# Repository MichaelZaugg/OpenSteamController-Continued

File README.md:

# Open Steam Controller - Continued

Welcome to the Open Steam Controller Continued Project!

This project is a fork of the [original Open Steam Controller](https://github.com/greggersaurus/OpenSteamController) by [Greg Gluszek](https://github.com/greggersaurus).

I hope to continue and improve upon the already amazing work done to deconstruct, document,
repurpose, and expand upon the Steam Controller firmware and hardware. As well as
provide a page of mods for those wanting to improve their own controllers with all
the information they need.

# The Steam Controller

The Steam Controller is a video game controller released by Valve Corporation
on November 10, 2015. This was part of Valve's initiative to give PC gamers the
option of a console-like experience.

Keeping some aspects familiar to modern video game controllers (i.e. a left analog stick,
four face buttons, two shoulder, and bumper buttons) while also changing up some of the
norms that we have come to expect (i.e. replacing the directional pad
and right analog stick with trackpads).

Additional details on the controller can be found on the official
[Product Page](https://store.steampowered.com/app/353370/Steam_Controller/)

# [Project Summary](./ProjectSummary.md)

Read about how this project came to be and the mind behind it.

# [Mods](./Mods/)

Take a look at some of the current mods for the Steam Controller in this directory.

# Notice and Warning

Please recognize that by utilizing any part of this project you are doing so at
your own risk. This is a reverse engineering effort and [we] make no claims to
have a complete understanding of the hardware [that we write] custom or modified
firmware for. Hopefully the testing [we] perform before publishing our findings and
modifications will prevent damage to your Steam Controller or anything you may
connect your Steam Controller to (i.e. the Nintendo Switch). However, [we] cannot
guarantee that.

Also please note this is being shared primarily for educational purposes. While
this may allow a user to do things such as use the Steam Controller on the
Nintendo Switch, please recognize that this is almost definitely going to be
coming with trade-offs compared to officially supported hardware and firmware.

Finally note that [we] say all of this with the hope of not discouraging anyone.
Please dive in and get your hands dirty. Just please be aware that there is a
(hopefully) very small, but non-zero, chance that a mistake could lead to
[bricked or broken hardware](./LoadingFirmware.md).

# Subproject Example

This section gives brief outlines and demonstrations (if applicable) of the
major efforts of this project. Further details on each Subproject can
be found in their respective directories.

## [Firmware](./Firmware/)

The work in this directory is geared towards creating a completely custom firmware
build for the Steam Controller. This project can be configured to have the
controller act as a development system that allows for querying peripherals
and exploring or verifying system behaviors. Additionally the project can
be configured for more practical purpose, such as behaving like a wired
Nintendo Switch controller.

Below are some videos demonstrating the different firmware builds:

Open Steam Controller: Nintendo Switch

Open Steam Controller: Development Board

# Contributing

This is an open source project, so please make use of this however you would
like (as long as it does not violate any licenses stated within).

If you would like to offer contributions back to this repo that would be great.
That could come in the form of issues/discussions on how this could be more
user friendly or by adding features or support that is not yet there.

Note that there are TODO documents for each Subproject. The idea
is to outline goals I would like to accomplish. If you want to help with any of
these that would be awesome. It would be even more awesome if you started a
conversation regarding your intentions so as to limit the chances of duplicated
effort or incongruous designs.

# Bugs and Issues

We will do our best to provide easy to use and robust software. However, there
will still most likely be bugs. If you find a bug, please report it.

The best way to report a bug is to use the Issues tab on GitHub.

When reporting a bug/issue, please make sure to provide sufficient details. Key
details to include are:

* Exactly what steps did you take?
* Can you reproduce the error by following your own steps?
* Do you have any files that make the bug occur (i.e. specific .musicxml file)?

# Resources and Influences

This section lists some projects that influenced this project, as well as links
to some resources that may continue to be helpful to stay current on.

## [Pilatomic Steam Controller Singer](https://gitlab.com/Pilatomic/SteamControllerSinger)

* Example of using the haptics to play music.
* Example of PC side code written in C using libusb.
* Allows for playing songs of any length, but at cost of controller being occupied by Singer software.

## [HID Joy-Con Whispering](https://github.com/shinyquagsire23/HID-Joy-Con-Whispering)

* Application for communicating with Pro Controller via USB HID.
* Helpful for Switch Faux Controller development to get USB communications in place.

## [Nintendo Switch Reverse Engineering](https://github.com/dekuNukem/Nintendo_Switch_Reverse_Engineering)

* Notes on Reverse Engineering of Nintendo Switch Controllers.
* Helpful details on HID communications with Pro Controller.

## [Standalone Steam Controller Driver](https://github.com/ynsta/steamcontroller)

* Source for breaking down some USB commands.
* Goal of this project is to be able to use Steam Controller as a game controller outside of the Steam platform.

## [Steam Controller Update News](http://store.steampowered.com/news/?appids=353370)

* Useful to get an idea of what changed from official firmware to firmware release.

## [UnBricking Steam Controller (Manual Firmware Update, Rollback)](https://steamcommunity.com/sharedfiles/filedetails/?id=572740074)

* Step by step guide on how to manually change the Steam Controller firmware.
* Much of this information is captured in [Loading Firmware](./LoadingFirmware.md).
  * [Loading Firmware](./LoadingFirmware.md) presents the information in the context of how it applies to Open Steam Controller Project and its Subprojects.

## Steam Communities

* [Official Group](http://steamcommunity.com/games/353370#announcements/detail/901091250587237164)
* [Custom Sounds Discussion](https://steamcommunity.com/app/353370/discussions/0/458607699626517823/)

# TODO

While a lot has been accomplished in this project thus far, there is still so much that
can be done with the Steam Controller (especially given the groundwork that has
been laid up to this point). In order to capture and track these ideas TODO documents
have been made for each Subproject. A good place to start is the top-level
[TODO Document](./TODO.md). This covers the highest level goals for the project
while providing links to Subproject specific TODOS.

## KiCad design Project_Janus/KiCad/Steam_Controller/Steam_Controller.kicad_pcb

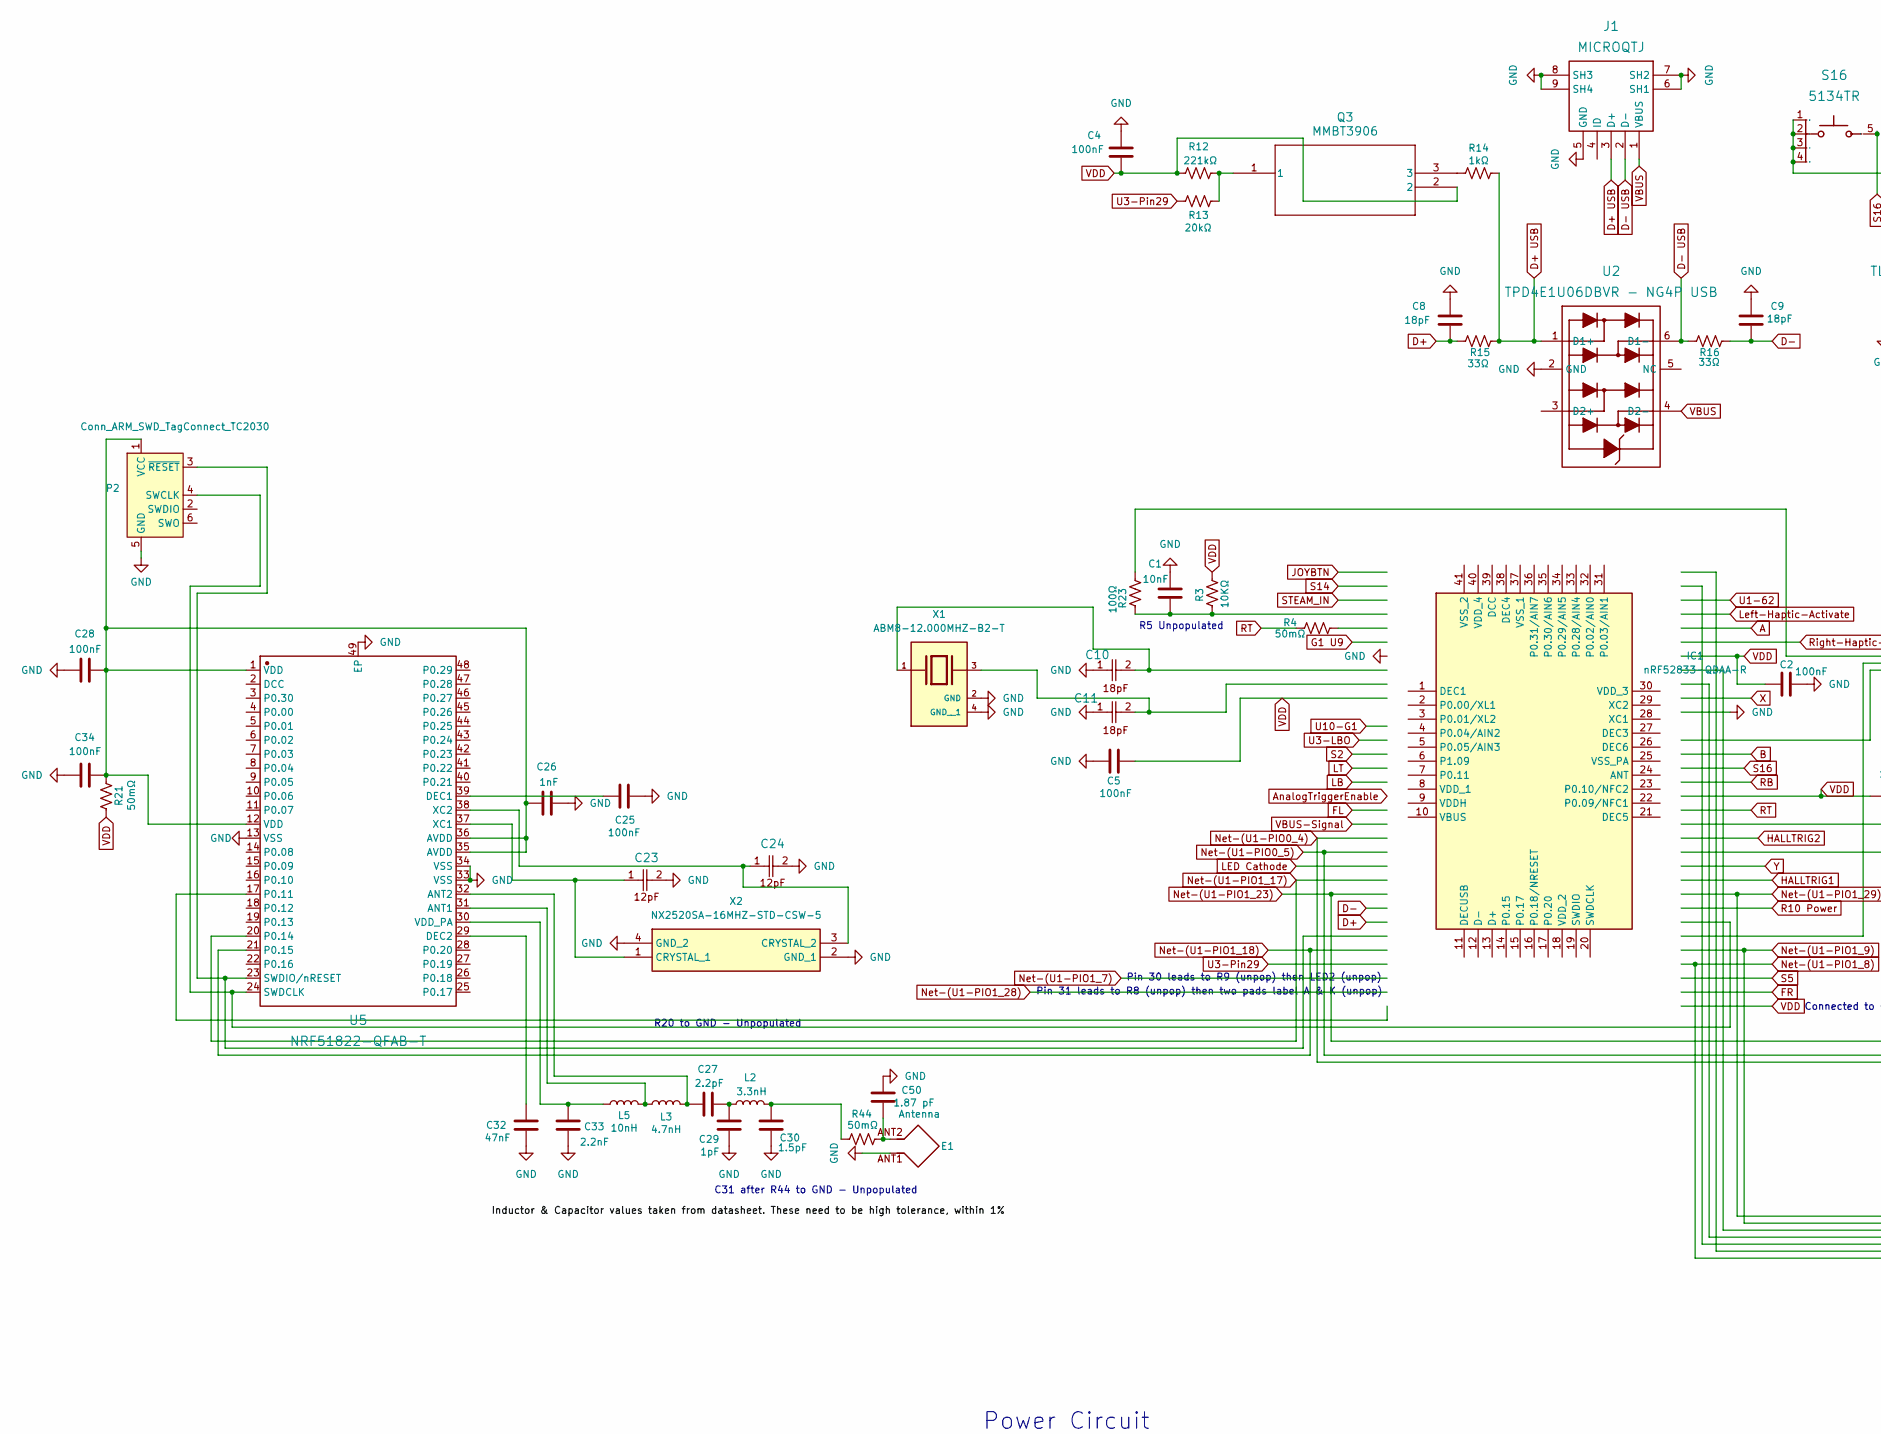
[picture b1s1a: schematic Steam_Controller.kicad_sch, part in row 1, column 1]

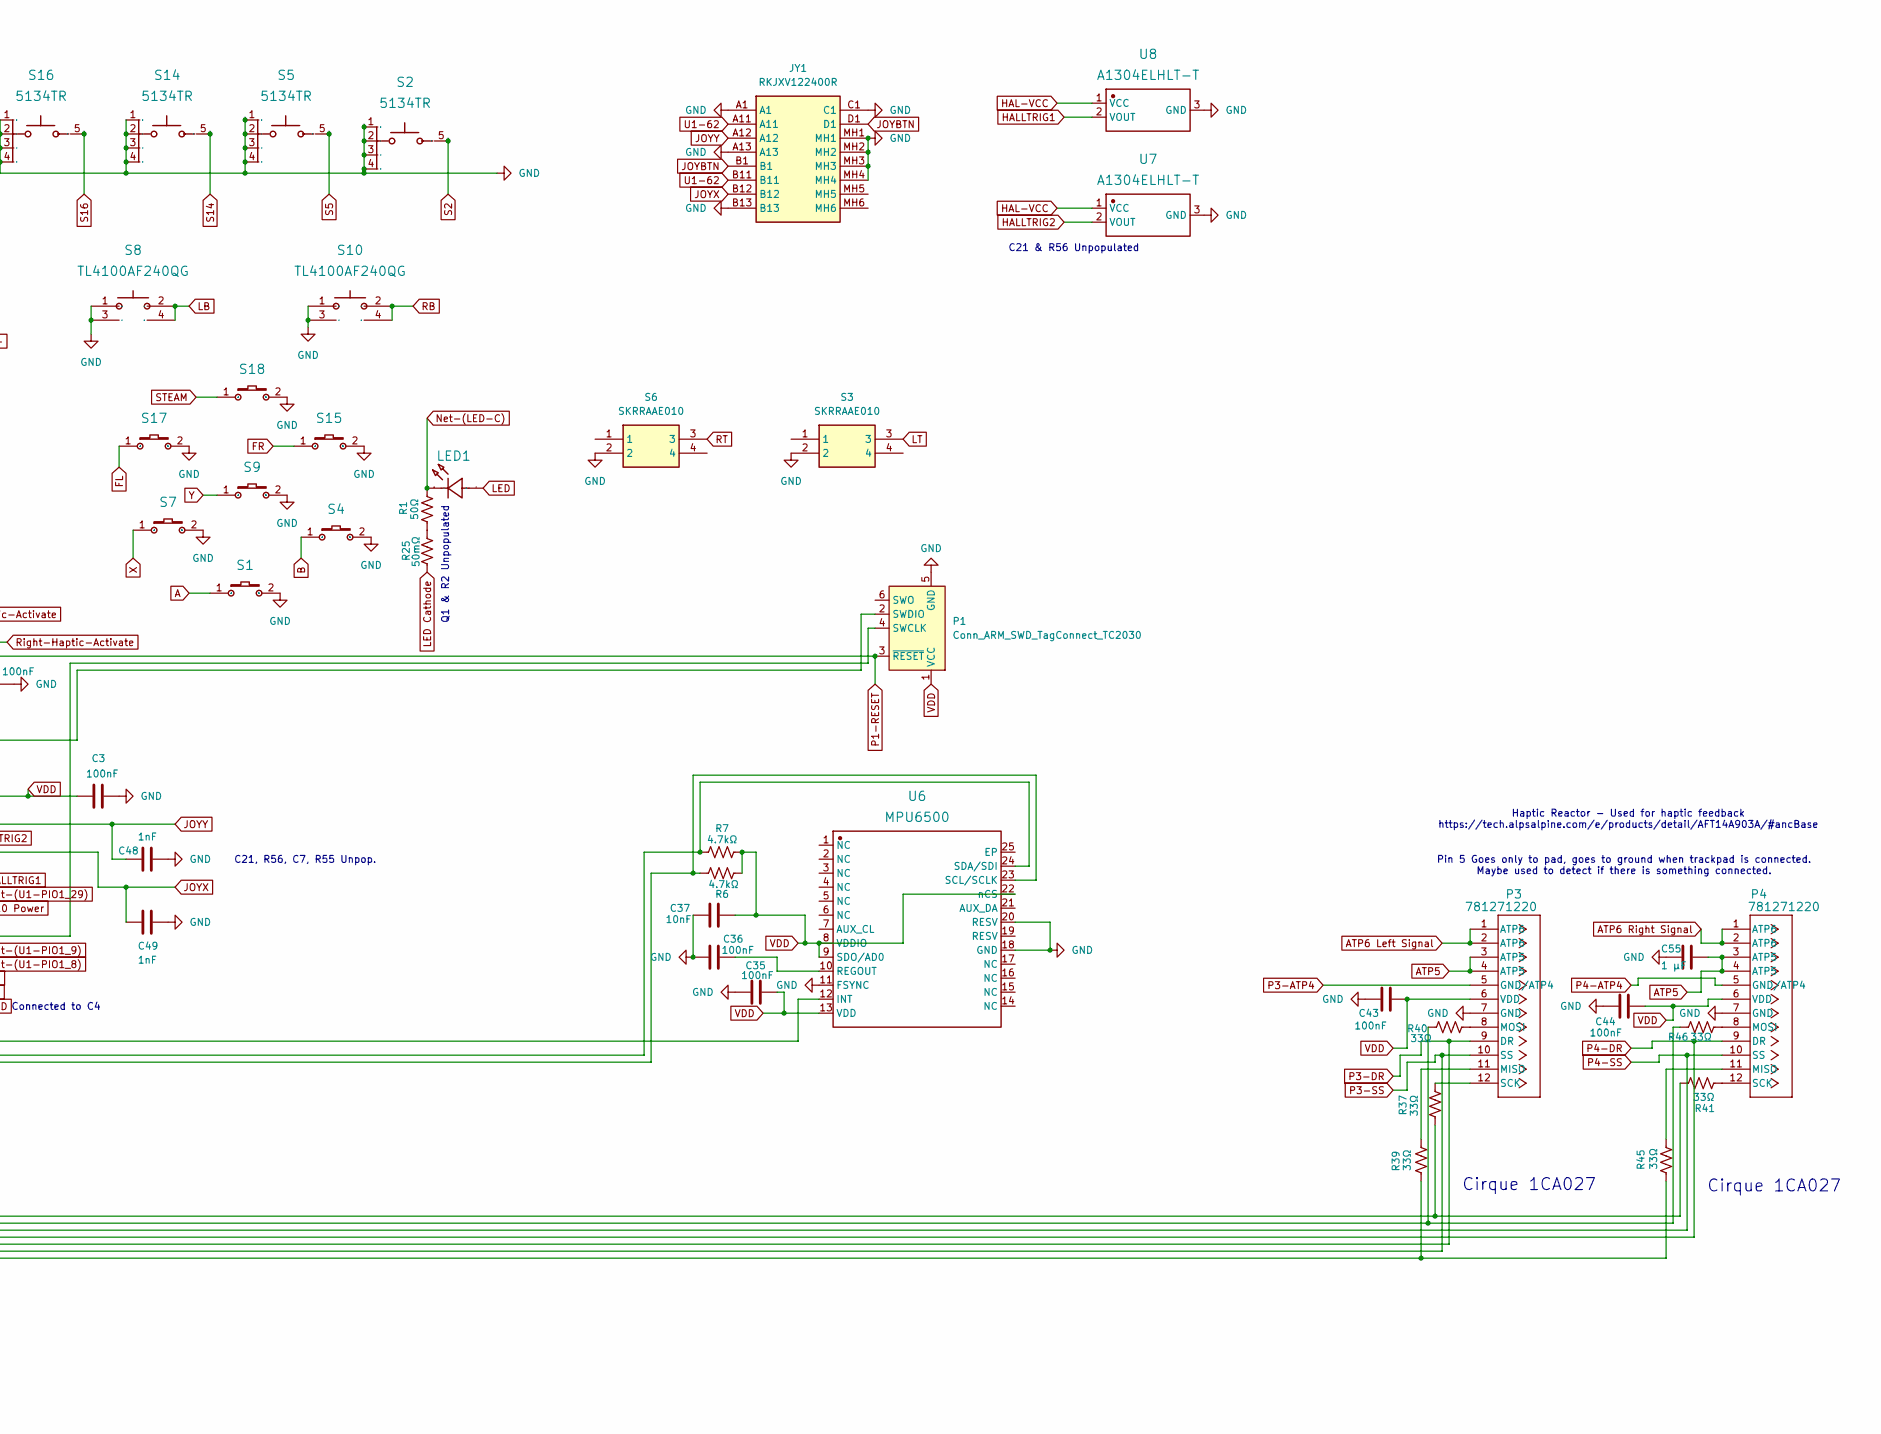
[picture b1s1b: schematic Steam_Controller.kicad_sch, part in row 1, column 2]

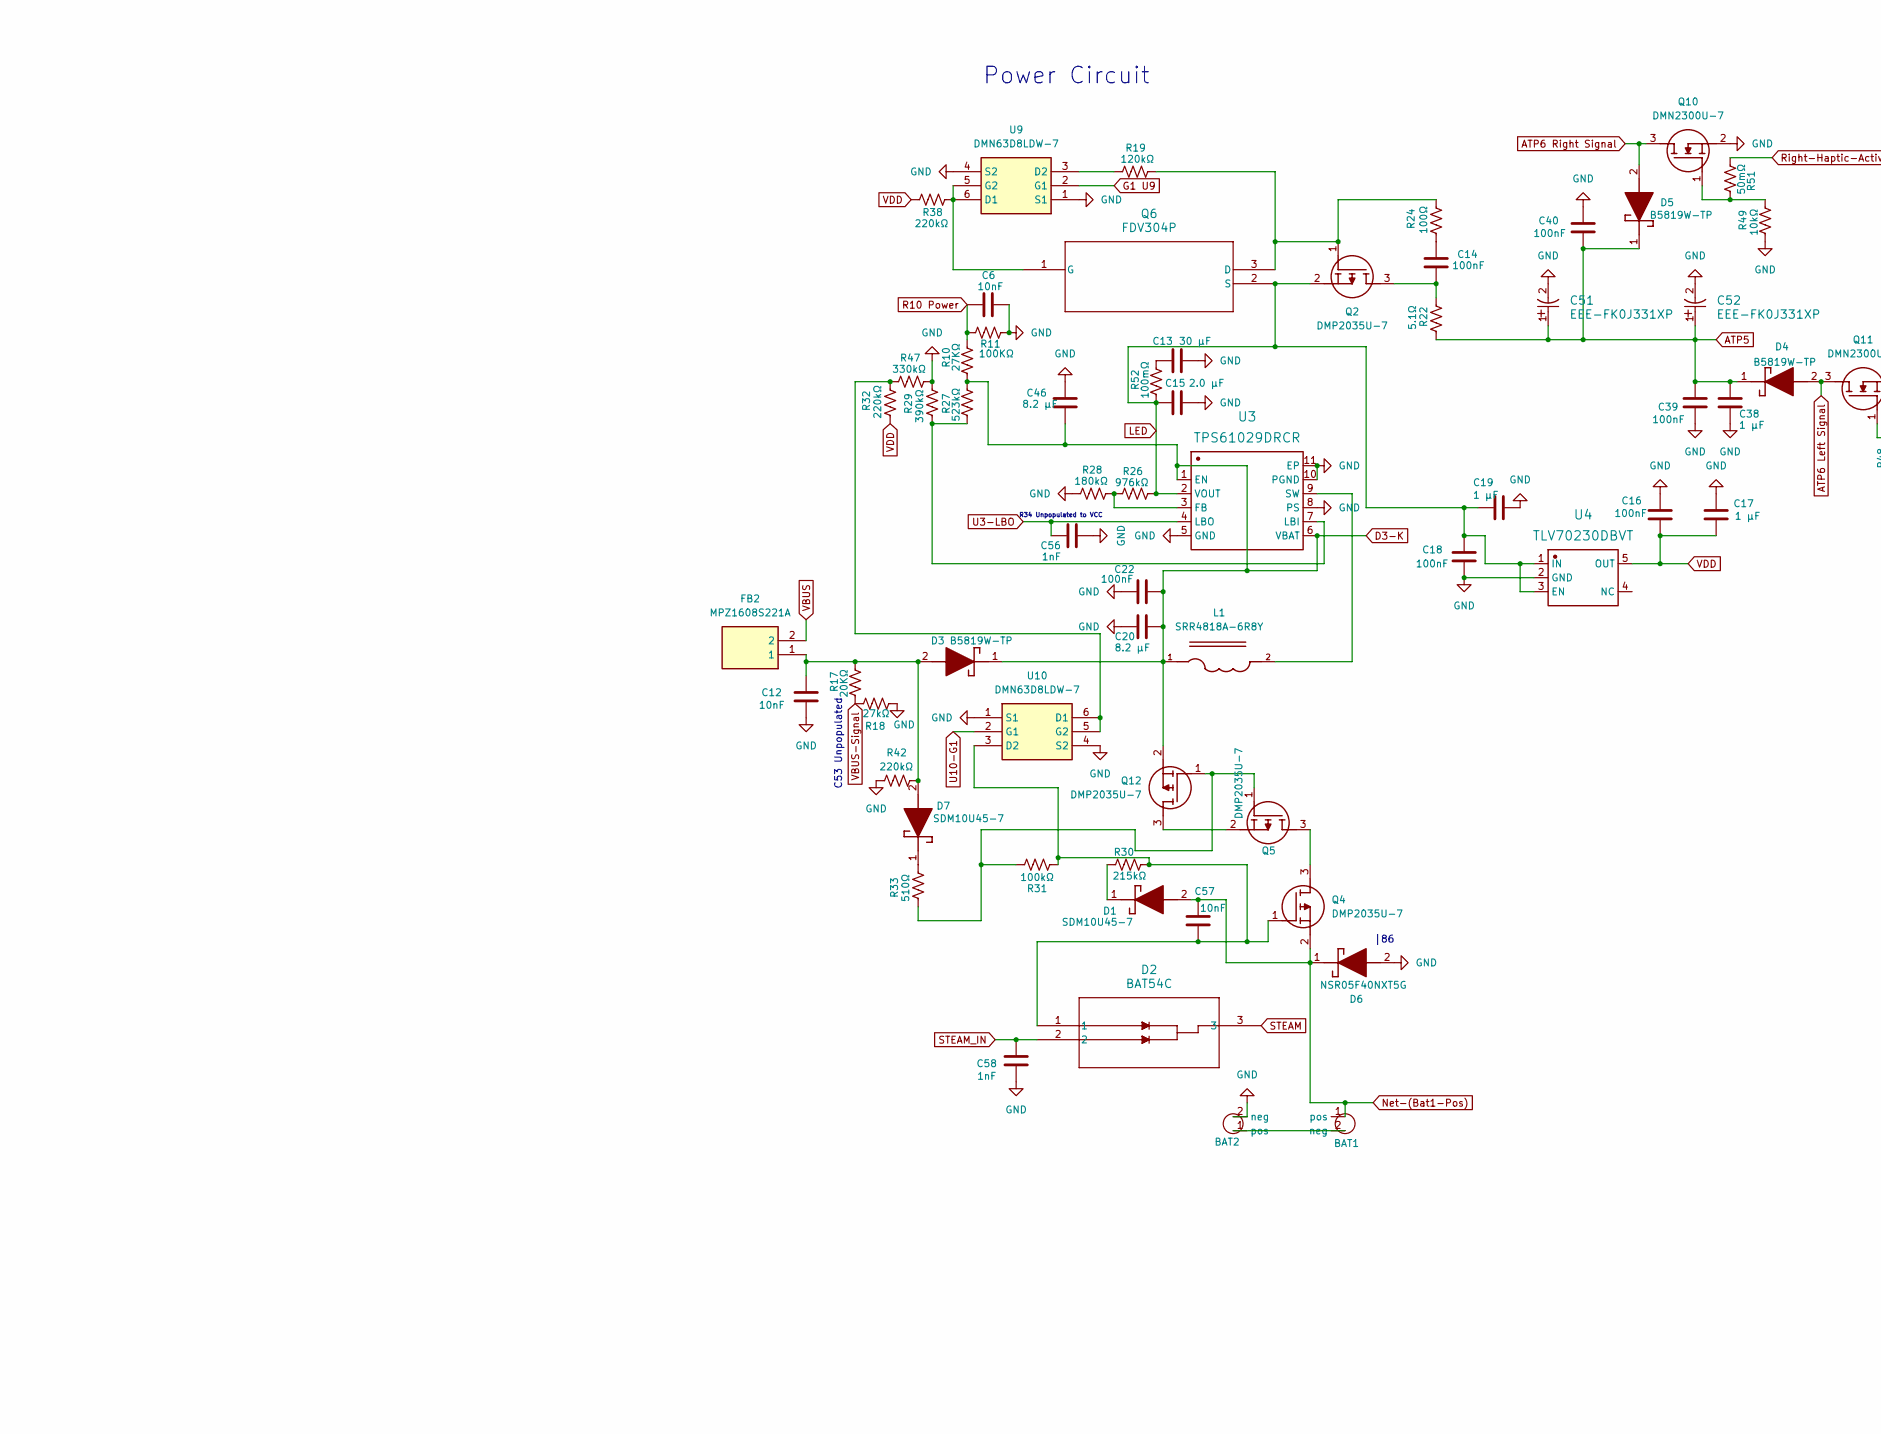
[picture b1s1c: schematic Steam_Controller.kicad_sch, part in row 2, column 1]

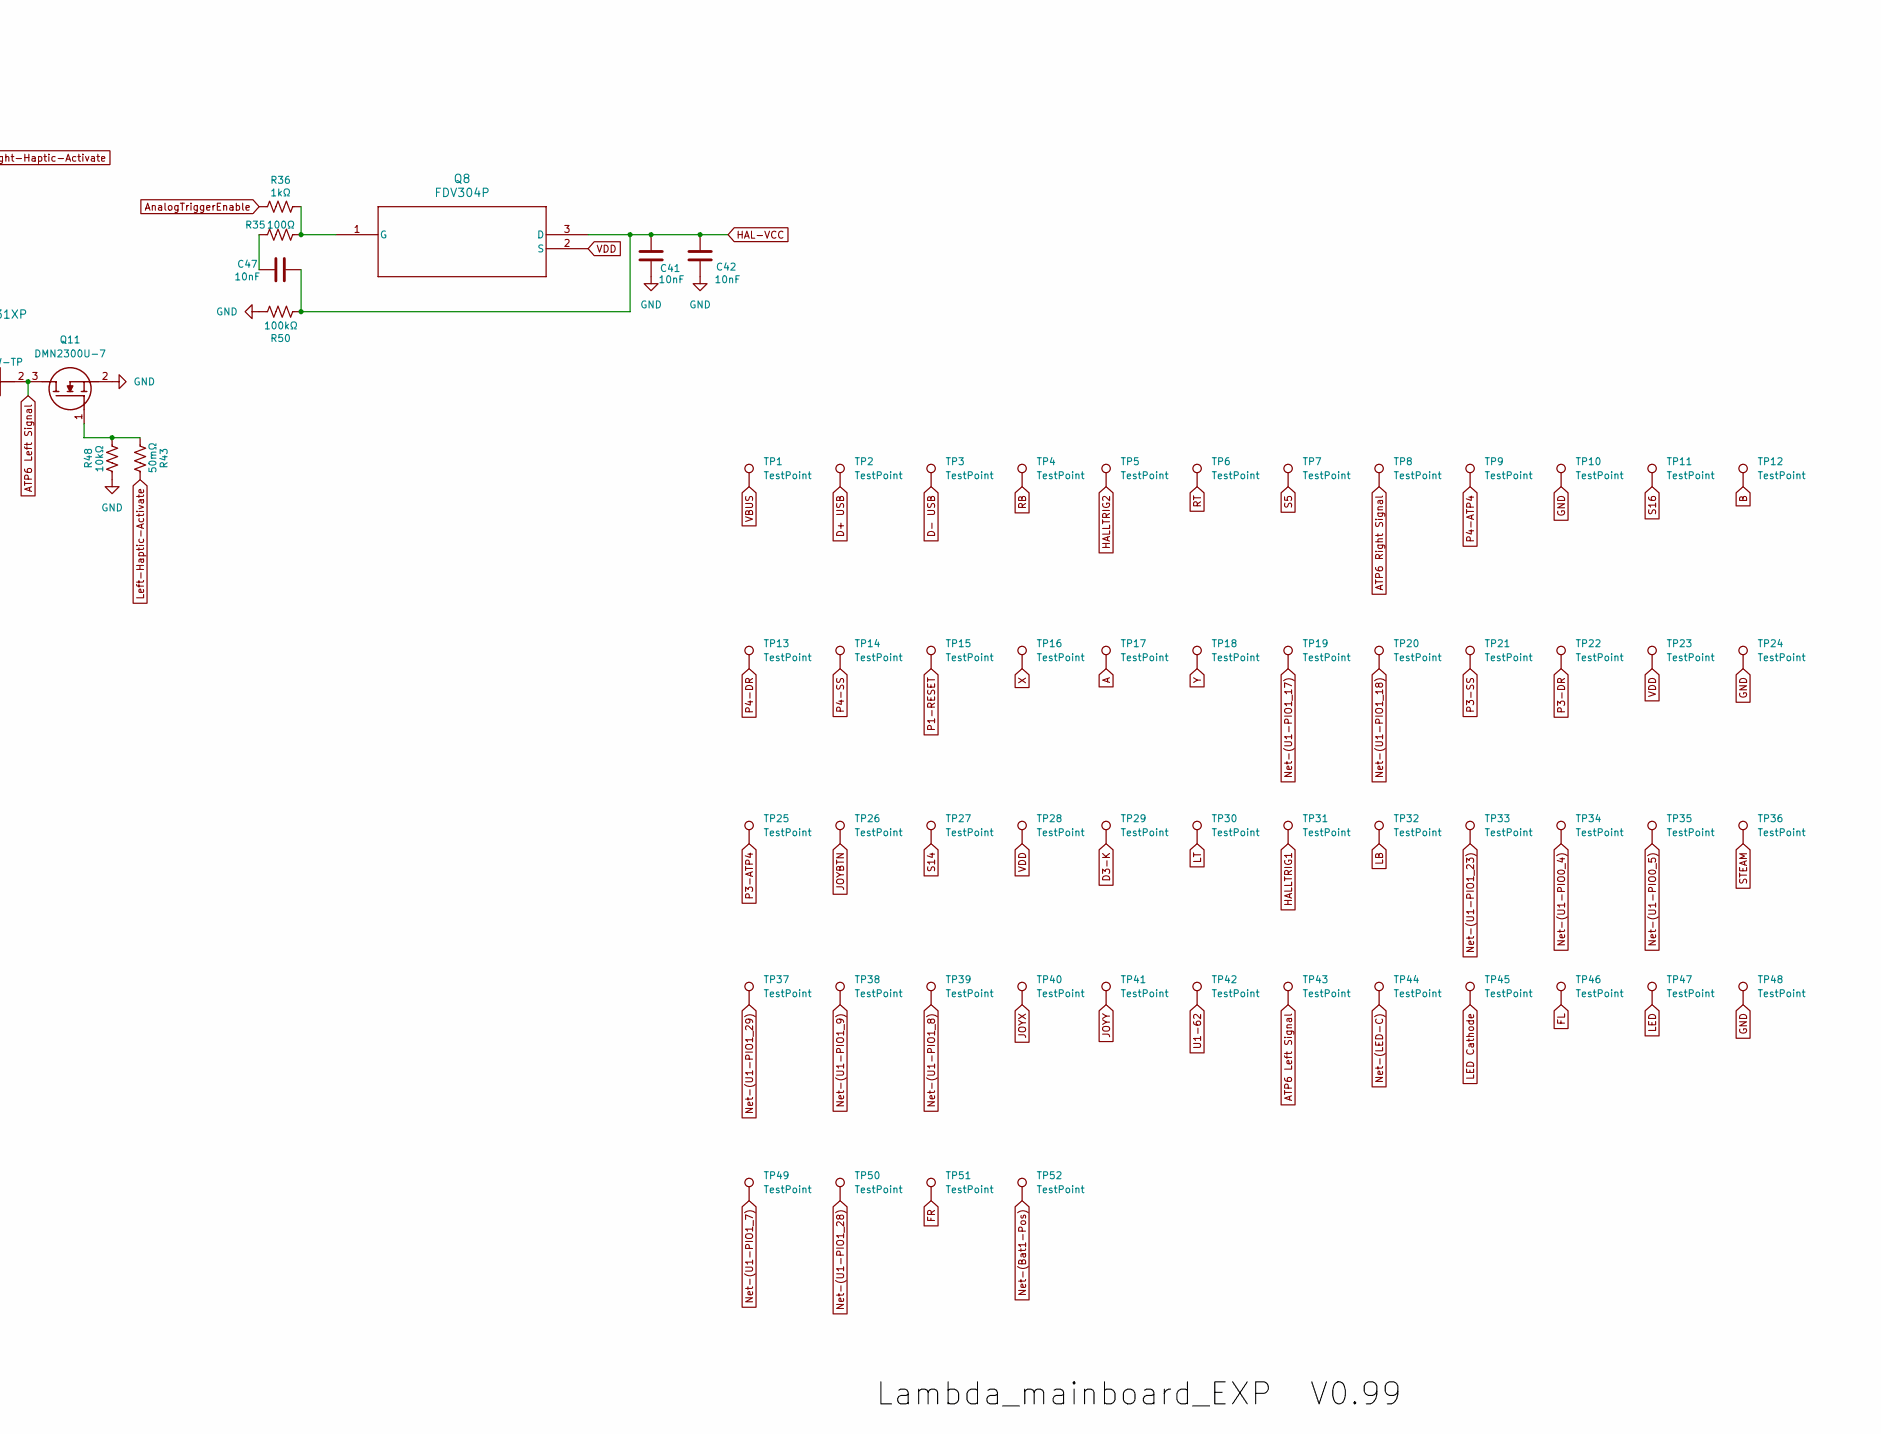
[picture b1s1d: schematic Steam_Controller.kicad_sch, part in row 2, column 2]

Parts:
BAT1, BAT2: BatteryPads
C1, C6, C12, C37, C41, C42, C47, C57: 10nF; C_0201_0603Metric
C2, C3, C4, C5, C14, C16, C18, C22, C25, C28, C34, C35, C36, C39, C43: 100nF; C_0201_0603Metric
C8, C9: 18pF; C_0201_0603Metric
C10, C11: C0402C180J3GACAUTO; C_0201_0603Metric
C13: 30 µF; C_1206_3216Metric
C15: 2.0 µF; C_0402_1005Metric
C17, C19, C38, C55: 1 µF; C_0402_1005Metric
C20, C46: 8.2 µF; C_0805_2012Metric
C23, C24: C0402C120F5GACTU; C_0201_0603Metric
C26, C48, C49, C56, C58: 1nF; C_0201_0603Metric
C27: 2.2pF; C_0201_0603Metric
C29: 1pF; C_0201_0603Metric
C30: 1.5pF; C_0201_0603Metric
C32: 47nF; C_0201_0603Metric
C33: 2.2nF; C_0201_0603Metric
C40, C44: 100nF; R_0201_0603Metric
C50: 1.87 pF; C_0201_0603Metric
C51, C52: EEE-FK0J331XP; CAP_EEFK_D8_PAN
D1, D7: SDM10U45-7; D_SOD-523; Mouser Part Number 621-SDM10U45
D2: BAT54C; SOT-23-3
D3, D4, D5: B5819W-TP; D_SOD-123; Mouser Part Number 833-B5819W-TP
D6: NSR05F40NXT5G; D_0201_0603Metric; Mouser Part Number 863-NSR05F40NXT5G
E1: Antenna; Antenna_footprint
FB2: MPZ1608S221A; L_0402_1005Metric; Mouser Part Number 810-MPZ1608S221A
IC1: nRF52833-QDAA-R; QFN40P500X500X90-41N; Manufacturer_Part_Number nRF52833-QDAA-R; Mouser Part Number 949-NRF52833-QDAA-R
J1: MICROQTJ; MICRO-USB-SMD_MICROQTJ-5P; Manufacturer Part MicroQTJ
JY1: RKJXV122400R; Mouser Part Number 688-RKJXV122400R
L1: SRR4818A-6R8Y; IND_SRR4818A-6R8Y; DigiKey_Part_Number SRR4818A-6R8YTR-ND
L2: 3.3nH; L_0201_0603Metric
L3: 4.7nH; L_0201_0603Metric
L5: 10nH; L_0201_0603Metric
LED1: E6C0805WWAY1UDA(1.1T_M); LED0805-RD_WHITE; Manufacturer Part E6C0805WWAY1UDA(1.1T M)
P1, P2: Conn_ARM_SWD_TagConnect_TC2030; Tag-Connect_TC2030-IDC-FP_2x03_P1.27mm_Vertical
P3, P4: 781271220; CON_781271220
Q2, Q4, Q5, Q12: DMP2035U-7; SOT-23-3; Manufacturer_Part_Number DMP2035U-7
Q3: MMBT3906; SOT-23-3
Q6, Q8: FDV304P; SOT-23-3
Q10, Q11: DMN2300U-7; SOT-23-3; Mouser Part Number 621-DMN2300U-7
R1: 50Ω; R_0201_0603Metric
R3: 10KΩ; R_0201_0603Metric
R4, R21, R25, R43, R44, R51: 50mΩ; R_0201_0603Metric
R6, R7: 4.7kΩ; R_0201_0603Metric
R10: 27KΩ; R_0201_0603Metric
R11: 100KΩ; R_0201_0603Metric
R12: 221kΩ; R_0201_0603Metric
R13: 20kΩ; R_0201_0603Metric
R14, R36: 1kΩ; R_0201_0603Metric
R15, R16, R37, R39, R40, R41, R45, R46: 33Ω; R_0201_0603Metric
R17: 20KΩ; R_0201_0603Metric
R18: 27kΩ; R_0201_0603Metric
R19: 120kΩ; R_0201_0603Metric
R22: 5.1Ω; R_1206_3216Metric
R23, R24, R35: 100Ω; R_0201_0603Metric
R26: 976kΩ; R_0201_0603Metric
R27: 523kΩ; R_0201_0603Metric
R28: 180kΩ; R_0201_0603Metric
R29: 390kΩ; R_0201_0603Metric
R30: 215kΩ; R_0201_0603Metric
R31, R50: 100kΩ; R_0201_0603Metric
R32, R38, R42: 220kΩ; R_0201_0603Metric
R33: 510Ω; R_0201_0603Metric
R47: 330kΩ; R_0201_0603Metric
R48, R49: 10kΩ; R_0201_0603Metric
R52: 100mΩ; R_0603_1608Metric
S1, S4, S7, S9, S15, S17: Steam_Controller_ButtonPads; BUTTONPADS
S2, S5, S14, S16: 5134TR; SW_5134TR
S3, S6: SKRRAAE010; SKRR; Mouser Part Number 688-SKRRAA
S8, S10: TL4100AF240QG; SW-SMD_TL4100AF240QG; Manufacturer Part TL4100AF240QG
S18: STEAM_Symbol; STEAM
TP1, TP2, TP3, TP4, TP5, TP6, TP7, TP8, TP9, TP10, TP11, TP12, TP13, TP14, TP15, TP16, TP17, TP18, TP19, TP20, TP21, TP22, TP23, TP24, TP25, TP26, TP27, TP28, TP29, TP30, TP31, TP32, TP33, TP34, TP35, TP36, TP37, TP38, TP39, TP40, TP41, TP42, TP43, TP44, TP45, TP46, TP47, TP48, TP49, TP50, TP51, TP52: TestPoint; Steam Controller Test Pad
U2: TPD4E1U06DBVR - NG4P USB; SOT-23-6; Manufacturer Part TPD4E1U06DBVR
U3: TPS61029DRCR; VSON-10-1EP_3x3mm_P0.5mm_EP1.2x2mm; Manufacturer Part TPS61029DRCR
U4: TLV70230DBVT; SOT-23-5; Manufacturer Part TLV70230DBVT
U5: NRF51822-QFAB-T; QFN-48_L6.0-W6.0-P0.40-TL-EP4.6; Manufacturer Part NRF51822-QFAB-T
U6: MPU6500; QFN-24_L3.0-W3.0-P0.40-BL-EP; Manufacturer Part MPU-6500
U7, U8: A1304ELHLT-T; SOT-23W; Manufacturer Part A1304ELHLT-T
U9, U10: DMN63D8LDW-7; SOT-363_SC-70-6; Mouser Part Number 621-DMN63D8LDW-7
X1: ABM8-12.000MHZ-B2-T; XTAL_ABM8-12.000MHZ-B2-T; PARTREV 44041
X2: NX2520SA-16MHZ-STD-CSW-5; NX2520SA16MHZSTDCSW5; Mouser Part Number 344-NX2520SA16MCSW5

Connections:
A: S1.1 (1_in), TP17.1 (1_1)
ATP5: C38.1, C39.1, C40.1, C51.1, C52.1, C55.1, D4.1 (K), D5.1 (K), P3.3 (ATP5), P3.4 (ATP5), P4.3 (ATP5), P4.4 (ATP5), R22.2
ATP6 Left Signal: D4.2 (A), P3.1 (ATP6), P3.2 (ATP6), Q11.3 (D), TP43.1 (1_1)
ATP6 Right Signal: D5.2 (A), P4.1 (ATP6), P4.2 (ATP6), Q10.3 (D), TP8.1 (1_1)
AnalogTriggerEnable: R36.2
B: S4.1 (1_in), TP12.1 (1_1)
D3-K: C20.1, C22.2, C46.2, D3.1 (K), L1.1, Q12.2 (S), R10.2, R27.1, TP29.1 (1_1), U3.1 (EN), U3.6 (VBAT)
D+: C8.1, R15.2
D+ USB: J1.3 (D+), R14.1, R15.1, TP2.1 (1_1), U2.1 (D1+)
D-: C9.1, R16.1
D- USB: J1.2 (D-), R16.2, TP3.1 (1_1), U2.6 (D1-)
FL: S17.1 (1_in), TP46.1 (1_1)
FR: S15.1 (1_in), TP51.1 (1_1)
G1 U9: U9.2 (G1)
GND: BAT2.2 (neg), C1.1, C2.1, C3.1, C4.2, C5.1, C6.1, C8.2, C9.2, C10.1, C11.1, C12.1, C13.1, C15.1, C16.1, C17.1, C18.1, C19.1, C20.2, C22.1, C23.2, C24.2, C25.1, C26.1, C28.2, C29.2, C30.1, C32.2, C33.2, C34.2, C35.2, C36.2, C37.2, C38.2, C39.2, C40.2, C41.2, C42.2, C43.2, C44.2, C46.1, C48.1, C49.1, C50.2, C51.2, C52.2, C55.2, C56.1, C58.2, D6.2 (A), E1.1 (ANT1), J1.5 (GND), J1.6 (SH1), J1.7 (SH2), J1.8 (SH3), J1.9 (SH4), JY1.A1, JY1.A13, JY1.B13, JY1.C1, JY1.MH1, JY1.MH2, JY1.MH3, JY1.MH4, P1.5 (GND), P2.5 (GND), P3.7 (GND), P4.7 (GND), Q10.2 (S), Q11.2 (S), R11.2, R18.1, R28.2, R29.1, R42.1, R47.1, R48.2, R49.2, R50.2, S1.2 (2_out), S2.1, S2.2, S2.3, S2.4, S3.2, S4.2 (2_out), S5.1, S5.2, S5.3, S5.4, S6.2, S7.2 (2_out), S8.1, S8.3, S9.2 (2_out), S10.1, S10.3, S14.1, S14.2, S14.3, S14.4, S15.2 (2_out), S16.1, S16.2, S16.3, S16.4, S17.2 (2_out), S18.2 (2_out), TP10.1 (1_1), TP24.1 (1_1), TP48.1 (1_1), U2.2 (GND), U3.5 (GND), U3.8 (PS), U3.10 (PGND), U3.11 (EP), U4.2 (GND), U5.13 (VSS), U5.33 (VSS), U5.34 (VSS), U5.49 (EP), U6.11 (FSYNC), U6.18 (GND), U6.20 (RESV), U7.3 (GND), U8.3 (GND), U9.1 (S1), U9.4 (S2), U10.1 (S1), U10.4 (S2), X1.2 (GND), X1.4 (GND__1), X2.2 (GND_1), X2.4 (GND_2); also elsewhere on the board
HAL-VCC: C41.1, C42.1, C47.1, Q8.3 (D), R50.1, U7.1 (VCC), U8.1 (VCC)
HALLTRIG1: TP31.1 (1_1), U8.2 (VOUT)
HALLTRIG2: TP5.1 (1_1), U7.2 (VOUT)
JOYBTN: JY1.B1, JY1.D1, TP26.1 (1_1)
JOYX: C49.2, JY1.B12, TP40.1 (1_1)
JOYY: C48.2, JY1.A12, TP41.1 (1_1)
LB: S8.2, S8.4, TP32.1 (1_1)
LED: C15.2, C18.2, C19.2, LED1.2 (A), Q2.2 (S), Q6.2 (S), R26.1, R52.2, TP47.1 (1_1), U3.2 (VOUT), U4.1 (IN), U4.3 (EN)
LED Cathode: R25.2, TP45.1 (1_1)
LT: S3.3, TP30.1 (1_1)
Left-Haptic-Activate: R43.2
unnamed: BAT1.2 (neg), BAT2.1 (pos)
unnamed: BAT1.1 (pos), C57.1, D1.2 (A), D6.1 (K), Q4.2 (S), TP52.1 (1_1)
unnamed: C1.2, R3.2, R23.2
unnamed: C10.2, X1.1
unnamed: C11.2, X1.3
unnamed: C13.2, R52.1
unnamed: C14.2, R24.2
unnamed: C27.1, C29.1, L2.1
unnamed: C30.2, L2.2, R44.1
unnamed: C47.2, R35.2
unnamed: D1.1 (K), R30.1
unnamed: C12.2, D3.2 (A), D7.2 (A), FB2.1, R17.2, R42.2
unnamed: D7.1 (K), R33.2
unnamed: C50.1, E1.2 (ANT2), R44.2
unnamed: LED1.1 (C), R1.1, TP44.1 (1_1)
unnamed: P2.4 (SWCLK), U5.24 (SWDCLK)
unnamed: C26.2, C28.1, C34.1, P2.1 (VCC), R21.1, U5.1 (VDD), U5.12 (VDD), U5.35 (AVDD), U5.36 (AVDD)
unnamed: P2.3 (~RESET), U5.23 (SWDIO/nRESET)
unnamed: P3.11 (MISO), R39.1
unnamed: P3.8 (MOSI), R40.1
unnamed: P3.12 (SCK), R37.1
unnamed: P4.11 (MISO), R45.1
unnamed: P4.8 (MOSI), R46.2
unnamed: P4.12 (SCK), R41.2
unnamed: C14.1, Q2.3 (D), R22.1
unnamed: Q2.1 (G), Q6.3 (D), R19.1, R24.1
unnamed: Q3.1, R12.1, R13.1
unnamed: Q3.3, R14.2
unnamed: Q4.3 (D), Q5.3 (D)
unnamed: C57.2, D2.1, Q4.1 (G), R30.2, R31.2, U10.3 (D2)
unnamed: Q6.1 (G), R38.1, U9.5 (G2), U9.6 (D1)
unnamed: Q8.1 (G), R35.1, R36.1
unnamed: Q10.1 (G), R49.1, R51.2
unnamed: Q11.1 (G), R43.1, R48.1
unnamed: Q5.2 (S), Q12.3 (D)
unnamed: Q5.1 (G), Q12.1 (G), R31.1, R33.1
unnamed: R1.2, R25.1
unnamed: R6.2, TP34.1 (1_1), U6.23 (SCL/SCLK)
unnamed: R7.2, TP35.1 (1_1), U6.24 (SDA/SDI)
unnamed: R39.2, R45.2, TP39.1 (1_1)
unnamed: R40.2, R46.1, TP38.1 (1_1)
unnamed: TP19.1 (1_1), U5.20 (P0.14)
unnamed: TP20.1 (1_1), U5.21 (P0.15)
unnamed: TP33.1 (1_1), U6.12 (INT)
unnamed: R37.2, R41.1, TP37.1 (1_1)
unnamed: R26.2, R28.1, U3.3 (FB)
unnamed: R27.2, R29.2, U3.7 (LBI)
unnamed: L1.2, U3.9 (SW)
unnamed: L3.1, L5.2, U5.31 (ANT1)
unnamed: C27.2, L3.2, U5.32 (ANT2)
unnamed: C25.2, U5.39 (DEC1)
unnamed: C32.1, U5.29 (DEC2)
unnamed: C33.1, L5.1, U5.30 (VDD_PA)
unnamed: C23.1, U5.37 (XC1), X2.1 (CRYSTAL_1)
unnamed: C24.1, U5.38 (XC2), X2.3 (CRYSTAL_2)
unnamed: C36.1, U6.10 (REGOUT)
unnamed: R19.2, U9.3 (D2)
unnamed: R32.1, R47.2, U10.5 (G2), U10.6 (D1)
P1-RESET: P1.3 (~RESET), R23.1, TP15.1 (1_1)
P3-ATP4: P3.5 (GND/ATP4), TP25.1 (1_1)
P3-DR: P3.9 (DR), TP22.1 (1_1)
P3-SS: P3.10 (SS), TP21.1 (1_1)
P4-ATP4: P4.5 (GND/ATP4), TP9.1 (1_1)
P4-DR: P4.9 (DR), TP13.1 (1_1)
P4-SS: P4.10 (SS), TP14.1 (1_1)
R10 Power: C6.2, R10.1, R11.1
RB: S10.2, S10.4, TP4.1 (1_1)
RT: R4.2, S6.3, TP6.1 (1_1)
Right-Haptic-Activate: R51.1
S2: S2.5
S5: S5.5, TP7.1 (1_1)
S14: S14.5, TP27.1 (1_1)
S16: S16.5, TP11.1 (1_1)
STEAM: D2.3, S18.1 (1_in), TP36.1 (1_1)
STEAM_IN: C58.1, D2.2
U1-62: JY1.A11, JY1.B11, TP42.1 (1_1)
U3-LBO: C56.2, U3.4 (LBO)
U3-Pin29: R13.2
U10-G1: U10.2 (G1)
VBUS: FB2.2, J1.1 (VBUS), TP1.1 (1_1), U2.4 (D2-)
VBUS-Signal: R17.1, R18.2
VDD: C2.2, C3.2, C4.1, C5.2, C16.2, C17.2, C35.1, C37.1, C43.1, C44.1, P1.1 (VCC), P3.6 (VDD), P4.6 (VDD), Q3.2, Q8.2 (S), R3.1, R6.1, R7.1, R12.2, R21.2, R32.2, R38.2, TP23.1 (1_1), TP28.1 (1_1), U4.5 (OUT), U6.8 (VDDIO), U6.9 (SDO/AD0), U6.13 (VDD), U6.22 (nCS)
X: S7.1 (1_in), TP16.1 (1_1)
Y: S9.1 (1_in), TP18.1 (1_1)

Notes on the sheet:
R20 to GND - Unpopulated
Pin 31 leads to R8 (unpop) then two pads label A & K (unpop)
Q1 & R2 Unpopulated
R5 Unpopulated
|86
C31 after R44 to GND - Unpopulated
Power Circuit
Connected to C4
Pin 5 Goes only to pad, goes to ground when trackpad is connected. Maybe used to detect if there is something connected.
R34 Unpopulated to VCC
Pin 30 leads to R9 (unpop) then LED2 (unpop)
Haptic Reactor - Used for haptic feedback https://tech.alpsalpine.com/e/products/detail/AFT14A903A/#ancBase
Cirque 1CA027
C53 Unpopulated
C21, R56, C7, R55 Unpop.
C21 & R56 Unpopulated

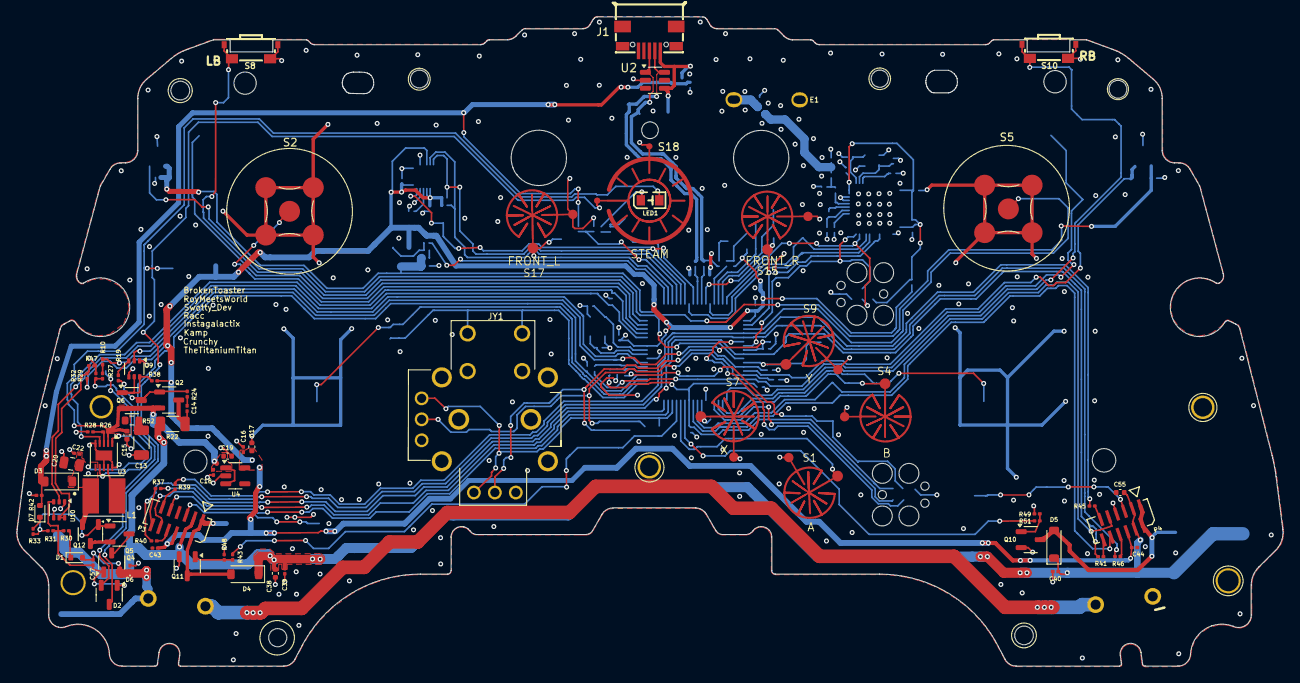
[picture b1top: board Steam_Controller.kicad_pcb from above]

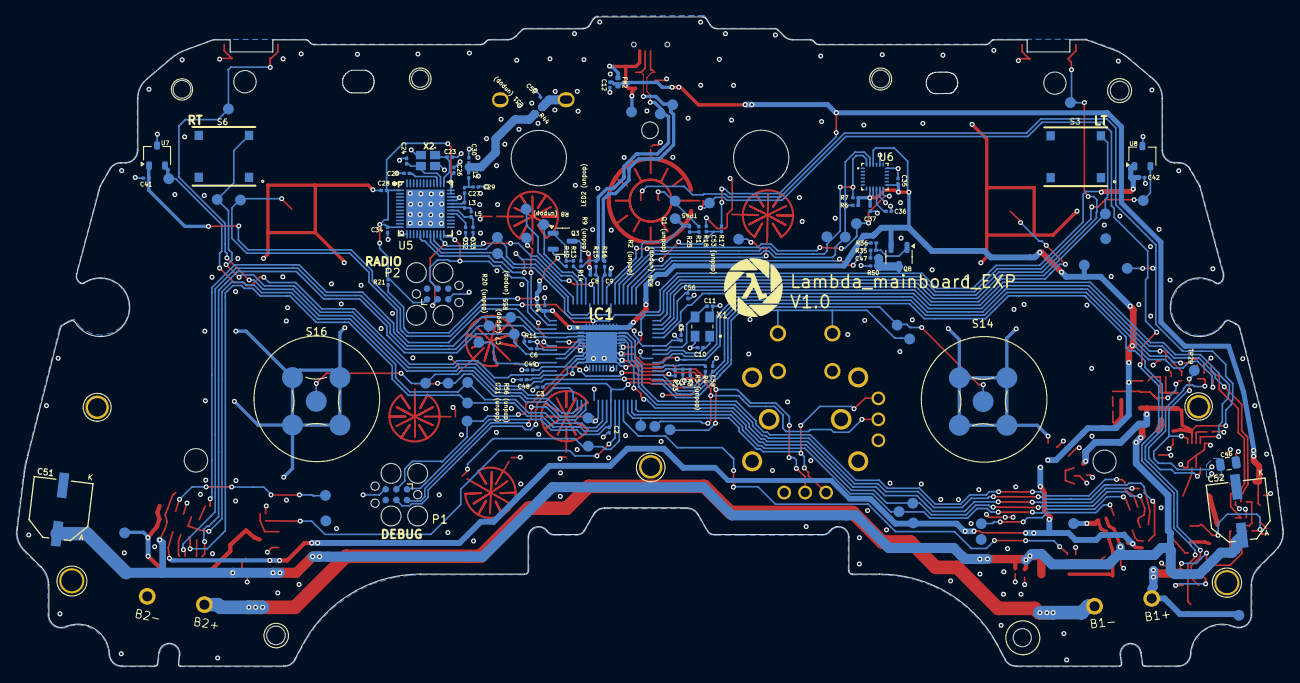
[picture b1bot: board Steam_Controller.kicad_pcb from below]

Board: 2 copper layers, 151.0 x 77.4 mm, 213 parts (77 on the bottom side), 103 nets.

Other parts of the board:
PAD1, PAD4: OuterPads2-5mm
PAD2, PAD3, PAD5: OuterPad2-2mm

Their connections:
GND: PAD1.1, PAD2.1, PAD3.1, PAD4.1, PAD5.1; also elsewhere on the board

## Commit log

2024-03-18 Documentation Updates
    Adding datasheets, manuals, other useful documentation for each IC on the board.
2024-03-18 Rename
2024-03-18 Updates to Pinouts and Datasheets
2024-03-18 Image Adjustments
2024-05-04 Rename Ribbon Cable Pinout to Cirque Board.md to Ribbon-Cable-Pinout-to-Cirque-Board.md
2024-05-04 Adding CAD file mods directory
2024-05-04 Reorganizing Project
    Adding a Mods folder and CAD mods as well as organizing the project.
2024-05-04 Link Fixes
2024-05-04 Added Right and Left Trackpad Arm STLs
    Version 1
2024-05-05 Battery Housing Baseplate v1
2024-05-06 Left and Right Battery Housing V1
2024-05-06 Added Missing Parts on SC & Organized.md
2024-10-14 Update Luna_maiboard_V000456-00_rev3.md
    Adding TODO for INT pin on MPU
2024-11-06 Pin numbering change
2024-11-06 Prep for Lambda_mainboard V1.0 Publishing
    Version 0.4. Images as placeholder.
2024-11-10 Happy 9 year
2024-11-10 Again
2024-11-27 Updated Schematic
    Cleaned up schematic, started connections from battery and tracing them.
2024-11-27 Updated PCB - Adding V0.5
    Started placing footprints for power and added battery terminals.
2024-11-27 Images, Updates, CAD
    Update to schematic, revised PCB, added 3D models, added new images.
2024-11-29 Fixed Board Outline/Updated 3D model
    Fixed board outline and 3D models. Added .stl file.
2025-01-20 Power Milestone Reached
    Traced power from the batteries to main processor
2025-01-21 New 3D images
2025-01-26 Update Luna_maiboard_V000456-00_rev3.md
    PIO1_10 trace to U10
2025-01-26 Update Luna_maiboard_V000456-00_rev3.md
    PIO0_2 trace to LBO U3
2025-01-27 Version 0.7
2025-01-27 Version 0.7 Schematic
2025-02-18 v0.8 Schematic
2025-02-19 Top and Bottom Corrections
2025-02-19 Ribbon Cable Images
2025-02-21 RibbonCable V1.0
2025-02-21 Haptic Reactor Used
2025-02-21 rev0.1 - added manufacturers recommendations
2025-02-23 Schematic V0.83
    Added X1, X2, and 4 capacitors
2025-02-23 Schematic V0.83
2025-02-25 OEM Firmware Tools
    Includes firmware from the controller and the official Valve firmware updater.
2025-03-09 Test
2025-03-09 Testv2
2025-03-09 Testv5
2025-03-09 Battery Latch Tension Holder CAD
    Contributed from Reddit User: MatthewUK_
2025-03-24 FCC Reports for Dongle and Steam Controller
    Adding them to the GitHub since they contain useful information.
2025-03-24 Prototype Steam Controller Directory
    Adding the Chell firmware.bin file to start as we find/ discover more prototype controller assets.
2025-03-26 Prototypes from u/lumpex999
2025-03-27 Shipped Chell Prototype
2025-03-27 Chell Internal-User Made
2025-05-06 Main Component List
    These are either the exact or equivalent substitute parts list for the main components on the PCB.
2025-05-19 SchematicV0.87 Resistors
2025-05-19 Added Resistors V0.87
2025-05-20 KiCad Link
2025-06-14 V0.9 Lambda Schematic
2025-06-19 KiCad For Collaboration
    V0.9 KiCad files for collaboration
2025-06-19 Adding Comments/Test
2025-06-19 Fixed Models - Updated Values
2025-06-20 Aligned Components
2025-06-20 Updated TODO in Schematic
    Added a new TODO objective in the schematic as a test for the discord bot
2025-06-20 added BLE Ghidra project
2025-06-20 added BLE readme
2025-06-20 Rename readme to readme.md
2025-07-17 Custom Rust Firmware
2025-07-18 Firmware in flashable state
2025-07-18 Added Firmware Build Script
2025-07-19 V0.99 Update
    Added trace updates from RoyMeetsWorld. Updated README. Added new images. Cleaned up some of the schematic and pcb.
2025-07-19 DRC Fixes / Updated 3D Model
2025-07-19 Prototype Gerber File Creation
2025-07-24 Added bash script for easy flashing of firmware
2025-07-25 Full codebase restructure
2025-07-31 Replaced MCU-6500 with BMI270 dual gyro
2025-07-31 Fix overlapping routing of INT trace to U11
2025-07-31 Replaced MicroUSB with USB-C
2025-08-03 Implemented GPIO digital functionality
2025-08-03 Fix OEM option for flash script
2025-08-03 Fixed OEM option in flashing script, but foreal this time
2025-08-04 Initialization stuff
2025-08-06 SC Dongle Project
2025-08-06 Updated Lambda README
2025-11-10 ECAD: Insert ESP32-S3, Delete Unnecessary Stuff, Organize
2025-11-13 Updated CAD for 3D printing
2025-11-13 Removing Old Version
2026-02-04 Connect trigger hall effects to power
2026-05-06 V1.0 Gerber files and cleanup
2026-05-15 Project Janus Init
2026-05-15 nRF52833 Setup KiCad
